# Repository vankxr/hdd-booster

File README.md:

# hdd-booster
This project consists of a simple PCB with two switching step-down regulators.
It aims to solve, or at least mitigate the low +5V rail current capacity of newer ATX consumer power supplies, which is a problem when trying to power lots of HDDs.
This problem is aggravated when adapters and splitters are used to expand the number of SATA/Molex power connectors.

## Short description
The board accepts power via a PCIe +12V aux power connector.
Since this board is best used on a NAS, typically there won't be any GPU installed, and thus there will be a +12V PCIe connector available.
The 12V from the PSU feeds both step-down regulators. Each regulator is capable of supplying about 5A, which should be enough for 4 power hungry HDDs.

## Authors

* **João Silva** - [vankxr](https://github.com/vankxr)

## License

The content of this repository is licensed under the [GNU General Public License v3.0](LICENSE).

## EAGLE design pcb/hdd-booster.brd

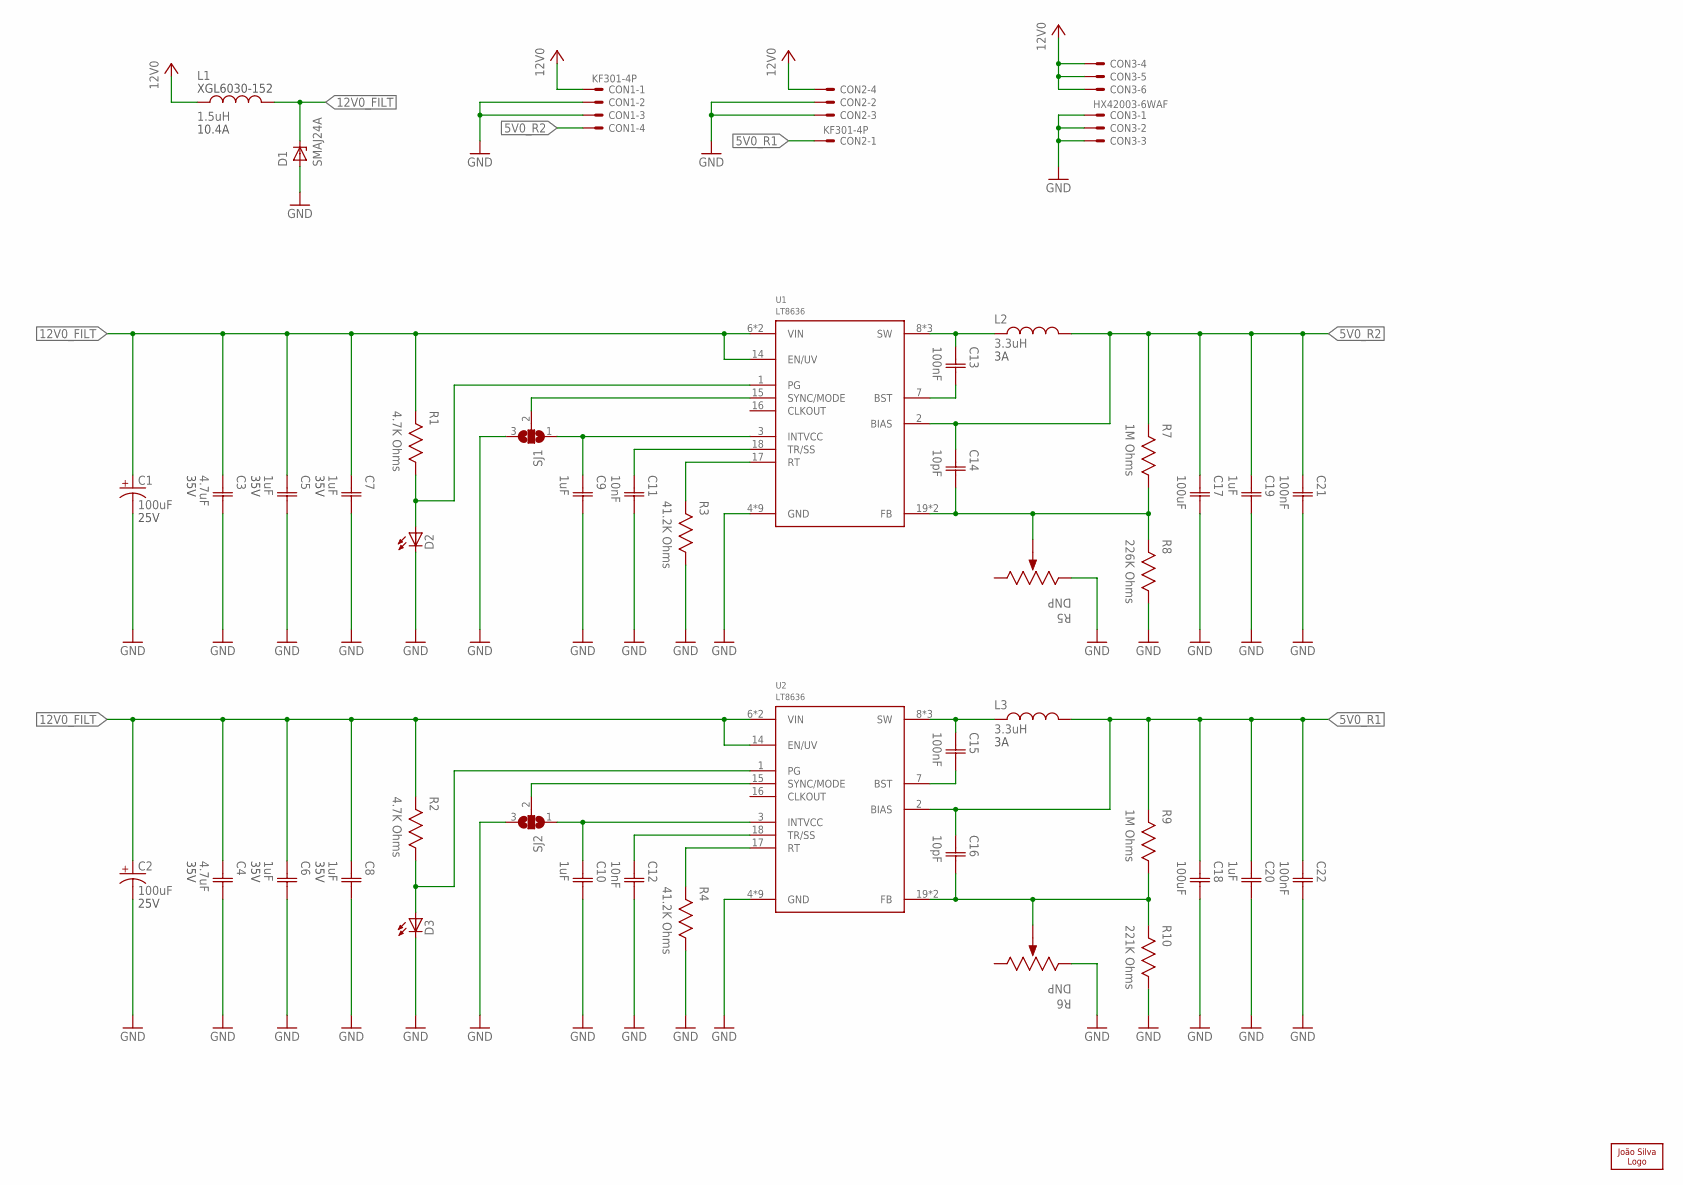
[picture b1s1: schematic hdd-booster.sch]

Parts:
C1, C2: 100uF; AL-CAP-CASE-D; VOLTAGE 25V
C3, C4: 4.7uF; CAP0603; VOLTAGE 35V
C5, C6, C7, C8: 1uF; CAP0402; VOLTAGE 35V
C9, C10, C19, C20: 1uF; CAP0402
C11, C12: 10nF; CAP0402
C13, C15, C21, C22: 100nF; CAP0402
C14, C16: 10pF; CAP0402
C17, C18: 100uF; CAP1206
CON1, CON2: KF301-4P
CON3: HX42003-6WAF
D1: SMAJ24A; DO214AC
D2, D3: LED1206; 1206
L1: 1.5uH; XGL6030
L2, L3: 3.3uH; XGL6030
LOGO1: JSILVA-5MM; JSILVA_5MM
R1, R2: 4.7K Ohms; RES0402
R3, R4: 41.2K Ohms; RES0402
R5, R6: DNP; POT3MM
R7, R9: 1M Ohms; RES0402
R8: 226K Ohms; RES0402
R10: 221K Ohms; RES0402
SJ1, SJ2: SJ2S; SJ2_S
U1, U2: LT8636; QFN20_ASYM_3X4_CORNER

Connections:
5V0_R1: C16.1 (C1), C18.1 (C1), C20.1 (C1), C22.1 (C1), CON2.1, L3.2, R9.2, U2.2 (BIAS)
5V0_R1_BST: C15.2 (C2), U2.7 (BST)
5V0_R1_FB: C16.2 (C2), R6.2 (WIPER), R9.1, R10.2, U2.19 (FB), U2.20 (FB)
5V0_R1_INTVCC: C10.1 (C1), SJ2.1, U2.3 (INTVCC)
5V0_R1_MODE: SJ2.2, U2.15 (SYNC/MODE)
5V0_R1_PG: D3.A, R2.1, U2.1 (PG)
5V0_R1_RT: R4.2, U2.17 (RT)
5V0_R1_SS: C12.1 (C1), U2.18 (TR/SS)
5V0_R1_SW: C15.1 (C1), L3.1, U2.8 (SW), U2.9 (SW), U2.10 (SW)
5V0_R2: C14.1 (C1), C17.1 (C1), C19.1 (C1), C21.1 (C1), CON1.4, L2.2, R7.2, U1.2 (BIAS)
5V0_R2_BST: C13.2 (C2), U1.7 (BST)
5V0_R2_FB: C14.2 (C2), R5.2 (WIPER), R7.1, R8.2, U1.19 (FB), U1.20 (FB)
5V0_R2_INTVCC: C9.1 (C1), SJ1.1, U1.3 (INTVCC)
5V0_R2_MODE: SJ1.2, U1.15 (SYNC/MODE)
5V0_R2_PG: D2.A, R1.1, U1.1 (PG)
5V0_R2_RT: R3.2, U1.17 (RT)
5V0_R2_SS: C11.1 (C1), U1.18 (TR/SS)
5V0_R2_SW: C13.1 (C1), L2.1, U1.8 (SW), U1.9 (SW), U1.10 (SW)
12V0: CON1.1, CON2.4, CON3.4, CON3.5, CON3.6, L1.1
12V0_FILT: C1.1 (+), C2.1 (+), C3.1 (C1), C4.1 (C1), C5.1 (C1), C6.1 (C1), C7.1 (C1), C8.1 (C1), D1.C, L1.2, R1.2, R2.2, U1.6 (VIN), U1.11 (VIN), U1.14 (EN/UV), U2.6 (VIN), U2.11 (VIN), U2.14 (EN/UV)
GND: C1.2 (-), C2.2 (-), C3.2 (C2), C4.2 (C2), C5.2 (C2), C6.2 (C2), C7.2 (C2), C8.2 (C2), C9.2 (C2), C10.2 (C2), C11.2 (C2), C12.2 (C2), C17.2 (C2), C18.2 (C2), C19.2 (C2), C20.2 (C2), C21.2 (C2), C22.2 (C2), CON1.2, CON1.3, CON2.2, CON2.3, CON3.1, CON3.2, CON3.3, D1.A, D2.C, D3.C, R3.1, R4.1, R5.1 (CCW), R6.1 (CCW), R8.1, R10.1, SJ1.3, SJ2.3, U1.4 (GND), U1.5 (GND), U1.12 (GND), U1.13 (GND), U1.21 (GND), U1.M1 (GND), U1.M2 (GND), U1.M3 (GND), U1.M4 (GND), U2.4 (GND), U2.5 (GND), U2.12 (GND), U2.13 (GND), U2.21 (GND), U2.M1 (GND), U2.M2 (GND), U2.M3 (GND), U2.M4 (GND)

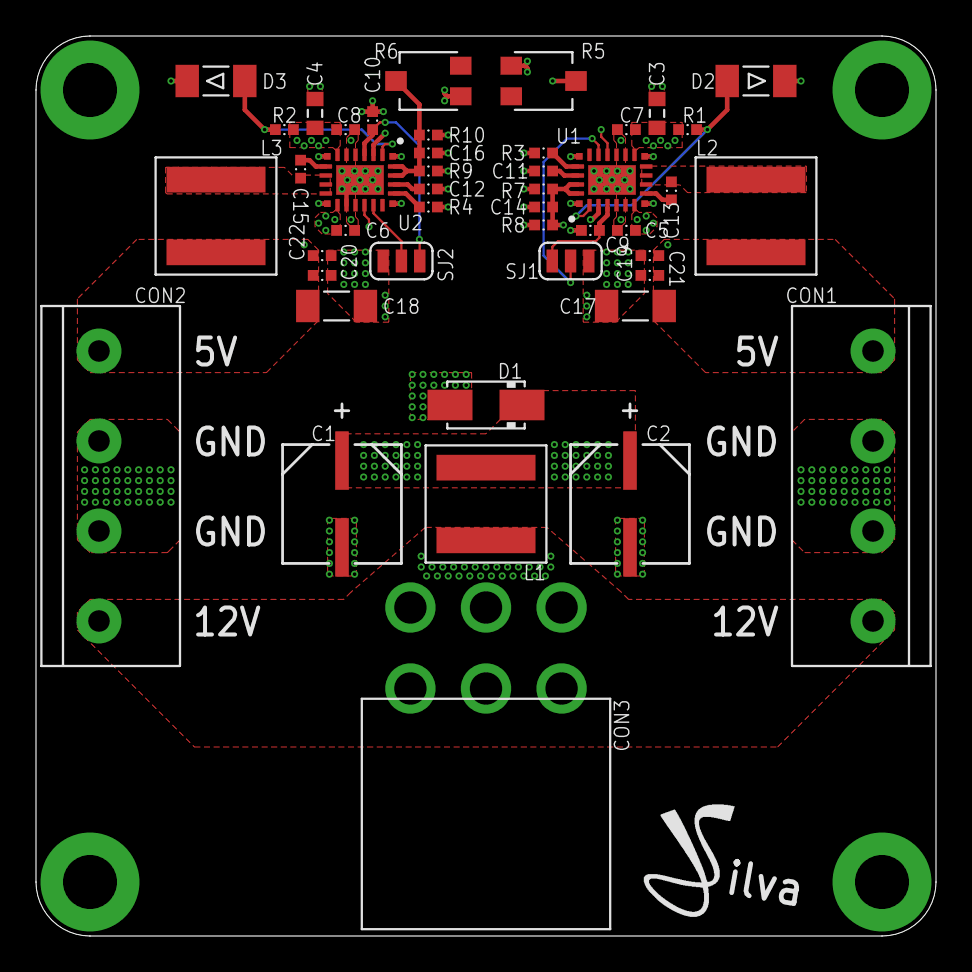
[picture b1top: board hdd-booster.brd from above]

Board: 8 copper layers, 50.0 x 50.0 mm, 46 parts (0 on the bottom side), 21 nets.
